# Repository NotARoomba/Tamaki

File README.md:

<h1 align="center">
  <br>
  
  <br>
  Tamaki
  <br>
</h1>

<h4 align="center">Project files for a custom Tamagotchi macropad.</h4>

<div align="center">

</div>

<p align="center">
  <a href="#key-features">Key Features</a> •
  <a href="#case-and-cad">Case & CAD</a> •
  <a href="#pcb">PCB</a> •
  <a href="#bom">BOM</a> •
  <a href="#credits">Credits</a> •
  <a href="#license">License</a>
</p>

<!---

--->

## Key Features

- 4 Configurable Buttons (Cherry MX)
- 2 Rotary Encoders (EC11)
- 1 OLED 128x32 Display
- 1 WS2812B RGB LED
- USB Type-C
- KMK firmware
- OLED-powered Tamagotchi

## Case and CAD

The case includes:

- 3D printed parts: a base and a top cover
- 1 laser-cut acrylic cover to protect electronics
- Assembled with 4x M3 bolts and 4x M3 heatset inserts

Designed in Fusion 360.

## PCB

Designed in KiCad with a custom logo. Notable points:

- `MX_V2` switch footprints
- EC11 encoder footprints
- OLED header and single RGB LED support

## BOM

Everything you need to build Tamaki:

- 4x Cherry MX Switches
- 4x Keycaps (DSA or any profile)
- 4x M3x5x4 Heatset Inserts
- 4x M3 Bolts
- 1x WS2812B RGB LED
- 1x 128x32 0.91" OLED Display
- 2x EC11 Rotary Encoders
- 1x XIAO RP2040
- 1x Case (2 printed parts + 1 acrylic cover)

## Credits

This project uses:

- [KiCad](https://www.kicad.org/)
- [Python](https://www.python.org/)
- [Fusion 360](https://www.autodesk.com/products/fusion-360/overview)

## You may also like...

- [Niveles De Niveles](https://github.com/NotARoomba/NivelesDeNiveles) – Real-time flood alert app
- [ROCKETMEN](https://github.com/NotARoomba/ROCKETMEN) – Custom flight controller files

## License

MIT

---

> [notaroomba.dev](https://notaroomba.dev) &nbsp;&middot;&nbsp;
> GitHub [@NotARoomba](https://github.com/NotARoomba)

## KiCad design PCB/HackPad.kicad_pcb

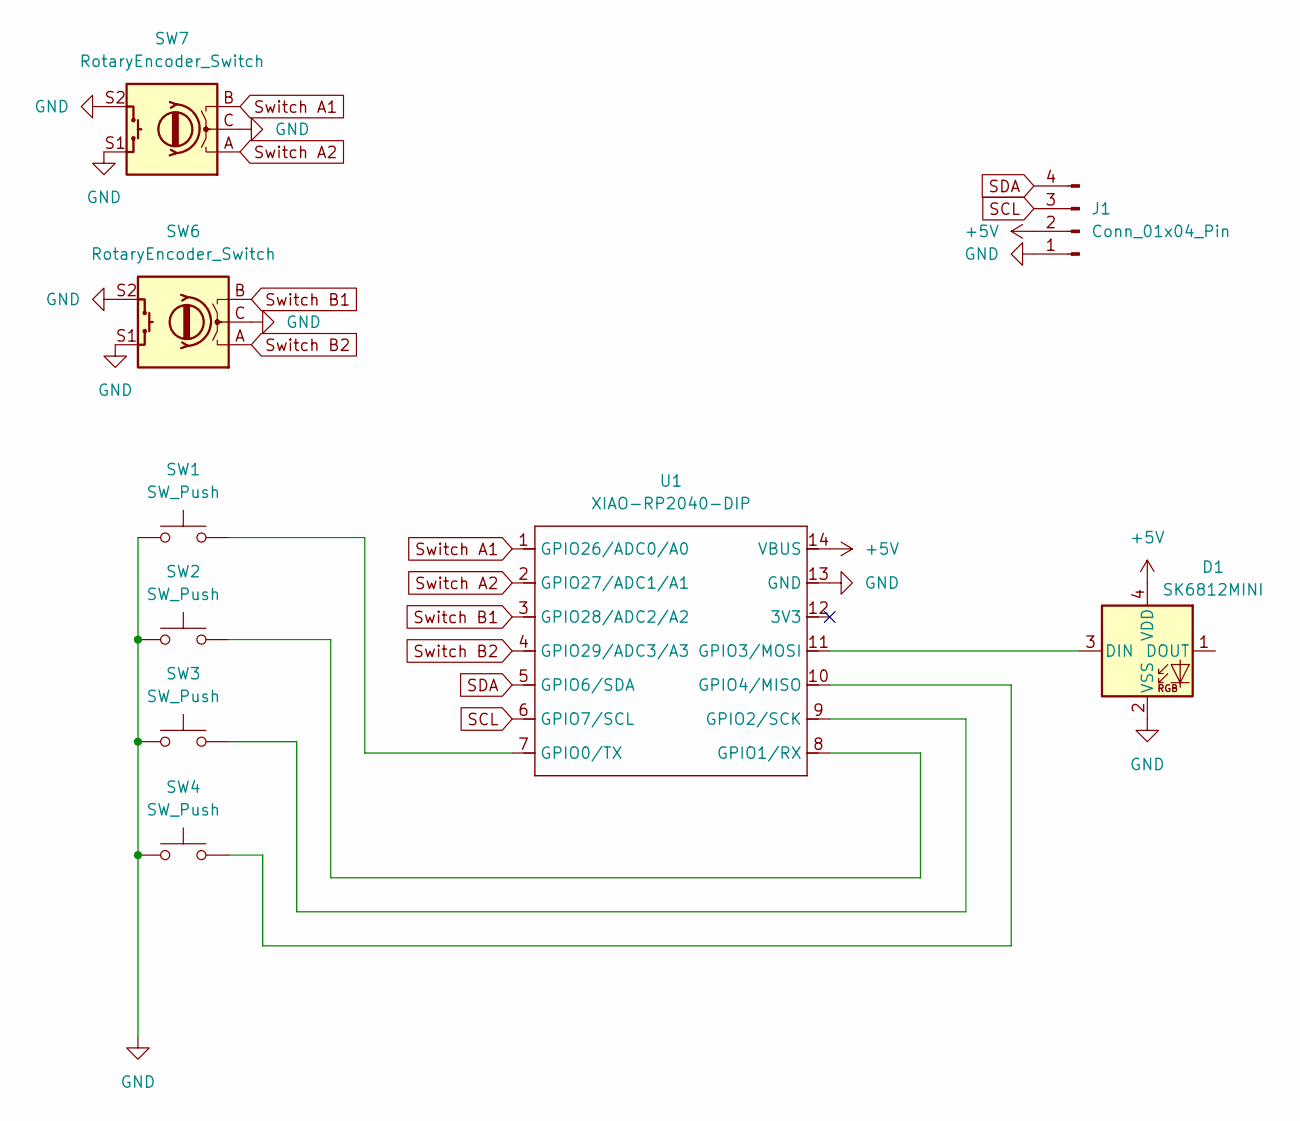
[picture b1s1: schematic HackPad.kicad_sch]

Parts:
D1: SK6812MINI; LED_SK6812MINI_PLCC4_3.5x3.5mm_P1.75mm
J1: Conn_01x04_Pin; SSD1306-0.91-OLED-4pin-128x32
SW1, SW2, SW3, SW4: SW_Push; SW_Cherry_MX_1.00u_PCB
SW6, SW7: RotaryEncoder_Switch; RotaryEncoder_Alps_EC11E-Switch_Vertical_H20mm
U1: XIAO-RP2040-DIP

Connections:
+5V: D1.4 (VDD), J1.2, U1.14 (VBUS)
GND: D1.2 (VSS), J1.1, SW1.1, SW2.1, SW3.1, SW4.1, SW6.C, SW6.S1, SW6.S2, SW7.C, SW7.S1, SW7.S2, U1.13 (GND)
unnamed: D1.3 (DIN), U1.11 (GPIO3/MOSI)
unnamed: SW1.2, U1.7 (GPIO0/TX)
unnamed: SW2.2, U1.8 (GPIO1/RX)
unnamed: SW3.2, U1.9 (GPIO2/SCK)
unnamed: SW4.2, U1.10 (GPIO4/MISO)
SCL: J1.3, U1.6 (GPIO7/SCL)
SDA: J1.4, U1.5 (GPIO6/SDA)
Switch A1: SW7.B, U1.1 (GPIO26/ADC0/A0)
Switch A2: SW7.A, U1.2 (GPIO27/ADC1/A1)
Switch B1: SW6.B, U1.3 (GPIO28/ADC2/A2)
Switch B2: SW6.A, U1.4 (GPIO29/ADC3/A3)

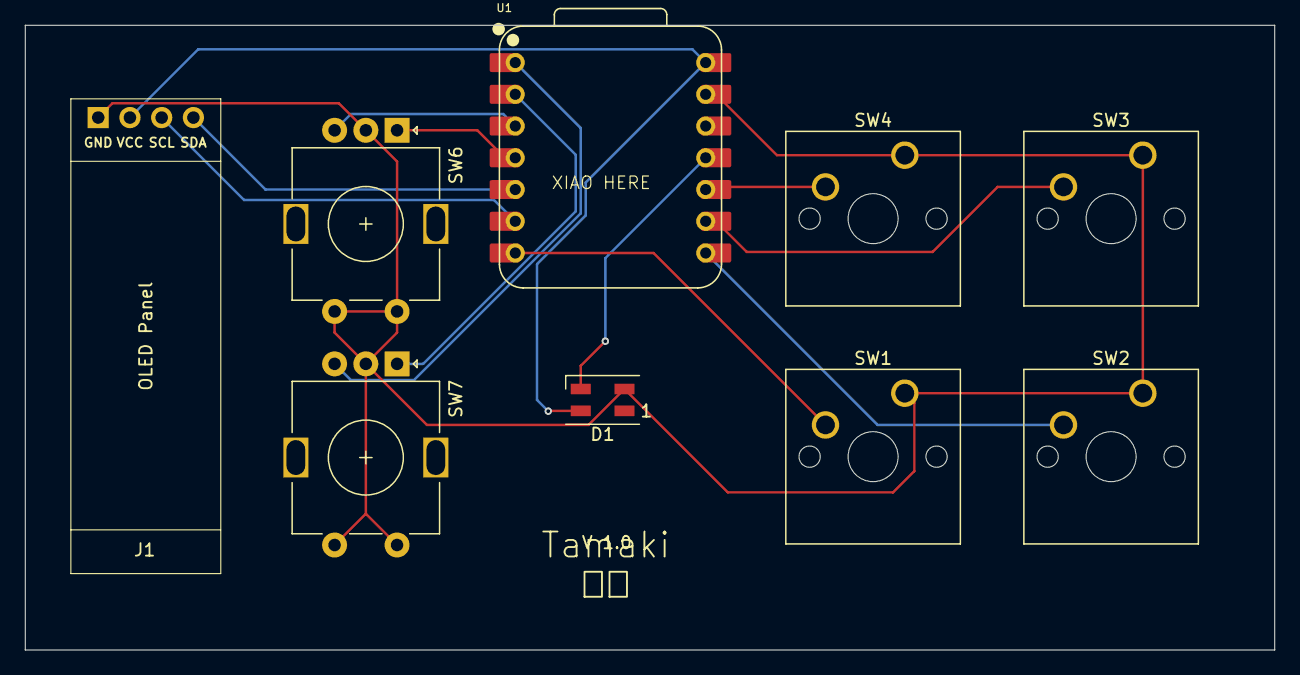
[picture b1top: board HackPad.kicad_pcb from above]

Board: 2 copper layers, 100.0 x 50.0 mm, 9 parts (0 on the bottom side), 13 nets.

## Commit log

2025-05-29 initial pcb and journal
2025-05-30 added files
2025-05-30 stuff
2025-10-03 step
